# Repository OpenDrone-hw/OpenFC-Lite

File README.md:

# OpenFC Lite 30x30

Open source Betaflight flight controller built on the RP2354B, 30.5 x 30.5 mm
mounting pattern, part of the incutec OpenDrone line.

## Specifications

| | |
|---|---|
| Firmware | Betaflight |
| MCU | RP2354B |
| IMU | BMI270 |
| Barometer | None |
| Blackbox | microSD |
| OSD | Analog and digital |
| UARTs | 4 |
| General-purpose I/O | 4 PWM-capable pins (GPIO28-31) on the 8-pin connector; the Betaflight target runs bidirectional DShot on them |
| RX | External, CRSF or SBUS |
| Input | 3-8S* LiPo (9.0-33.6 V) |
| BEC | 10 V switchable + 5 V always-on, 3.5 A |
| Current sense | Yes |
| USB | USB-C |
| Mounting | 30.5 x 30.5 mm, 4.0 mm holes |
| Dimensions | 37.9 x 37.9 mm |
| PCB | 6-layer, 1.6 mm |

* Also runs on 2S; the 10 V VTX output then follows the battery voltage instead of holding 10 V.

Technical write-up, part list and layout constraints: [AGENTS.md](AGENTS.md).

## Firmware

Betaflight, target `OPENFC_LITE_RP2350B`. The image is in
[`firmware/`](firmware/); older ones are in `firmware/archive/`.

If the analog OSD stays blank, run `feature -LED_STRIP` and then `save` in the
Betaflight Configurator CLI (the LED strip is then off). A firmware update
that runs the OSD and the LED strip together is in progress.

## In the line

What pairs with what, and what is available:
[opendrone.be](https://opendrone.be).

## Contributing

See [CONTRIBUTING.md](CONTRIBUTING.md).

## License

Hardware licensed under [CERN-OHL-S-2.0](https://ohwr.org/cern_ohl_s_v2.txt),
see [LICENSE](LICENSE).

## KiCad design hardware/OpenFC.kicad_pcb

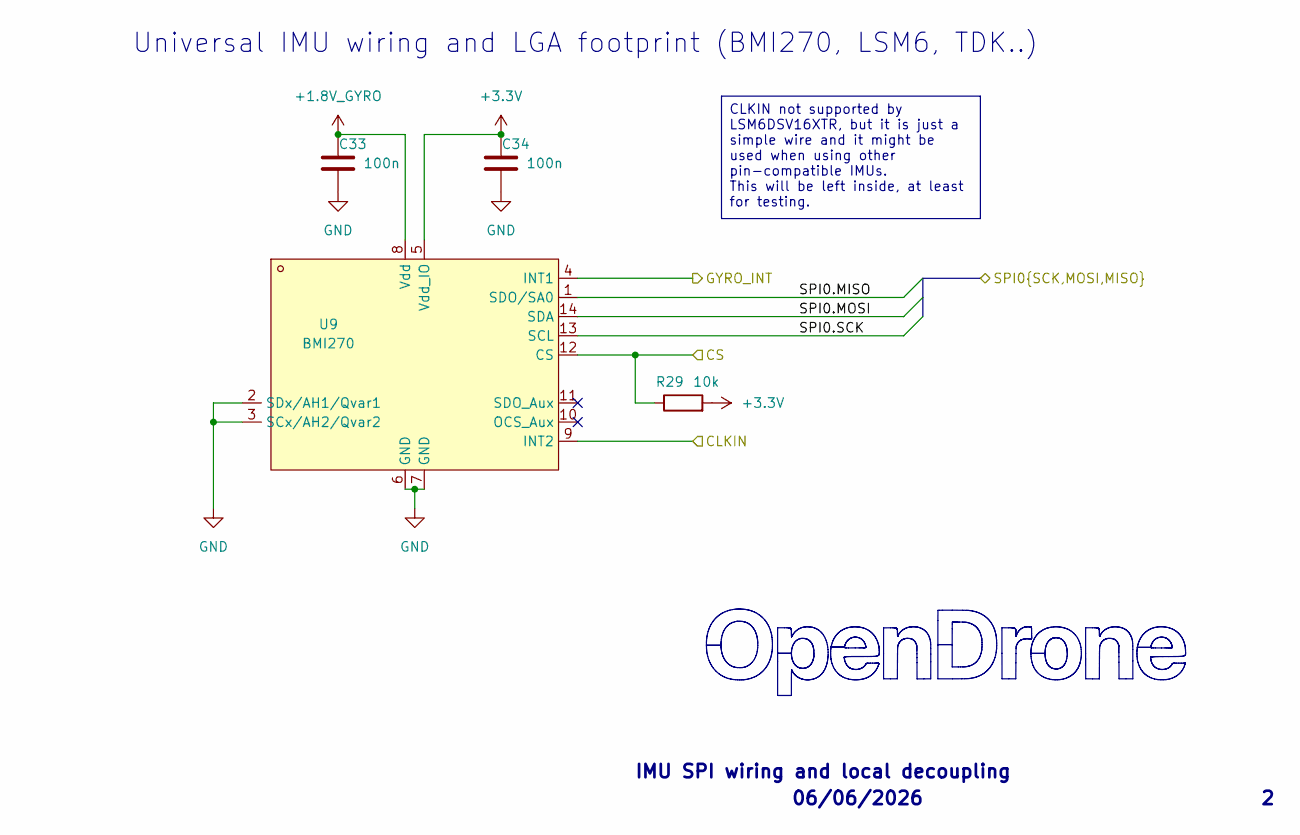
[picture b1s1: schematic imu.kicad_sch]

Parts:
C33, C34: 100n; C_0201_0603Metric; MPN GRM033R61E104KE14D; LCSC C76939
R29: 10k; R_0201_0603Metric; MPN RC0201FR-0710KL; LCSC C106225
U9: BMI270; LGA-14_L3.0-W2.5-P0.50-BR; MPN BMI270; LCSC C2836813

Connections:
+1.8V_GYRO: C33.1, U9.8 (Vdd); also elsewhere on the board
+3.3V: C34.1, R29.2, U9.5 (Vdd_IO); also elsewhere on the board
/IMU/CLKIN: U9.9 (INT2); also elsewhere on the board
/IMU/CS: R29.1, U9.12 (CS); also elsewhere on the board
/IMU/GYRO_INT: U9.4 (INT1); also elsewhere on the board
/IMU/SPI0.MISO: U9.1 (SDO/SA0); also elsewhere on the board
/IMU/SPI0.MOSI: U9.14 (SDA); also elsewhere on the board
/IMU/SPI0.SCK: U9.13 (SCL); also elsewhere on the board
GND: C33.2, C34.2, U9.2 (SDx/AH1/Qvar1), U9.3 (SCx/AH2/Qvar2), U9.6 (GND), U9.7 (GND); also elsewhere on the board

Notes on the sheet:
06/06/2026
IMU SPI wiring and local decoupling
Universal IMU wiring and LGA footprint (BMI270, LSM6, TDK..)
CLKIN not supported by LSM6DSV16XTR, but it is just a simple wire and it might be used when using other pin-compatible IMUs. This will be left inside, at least for testing.

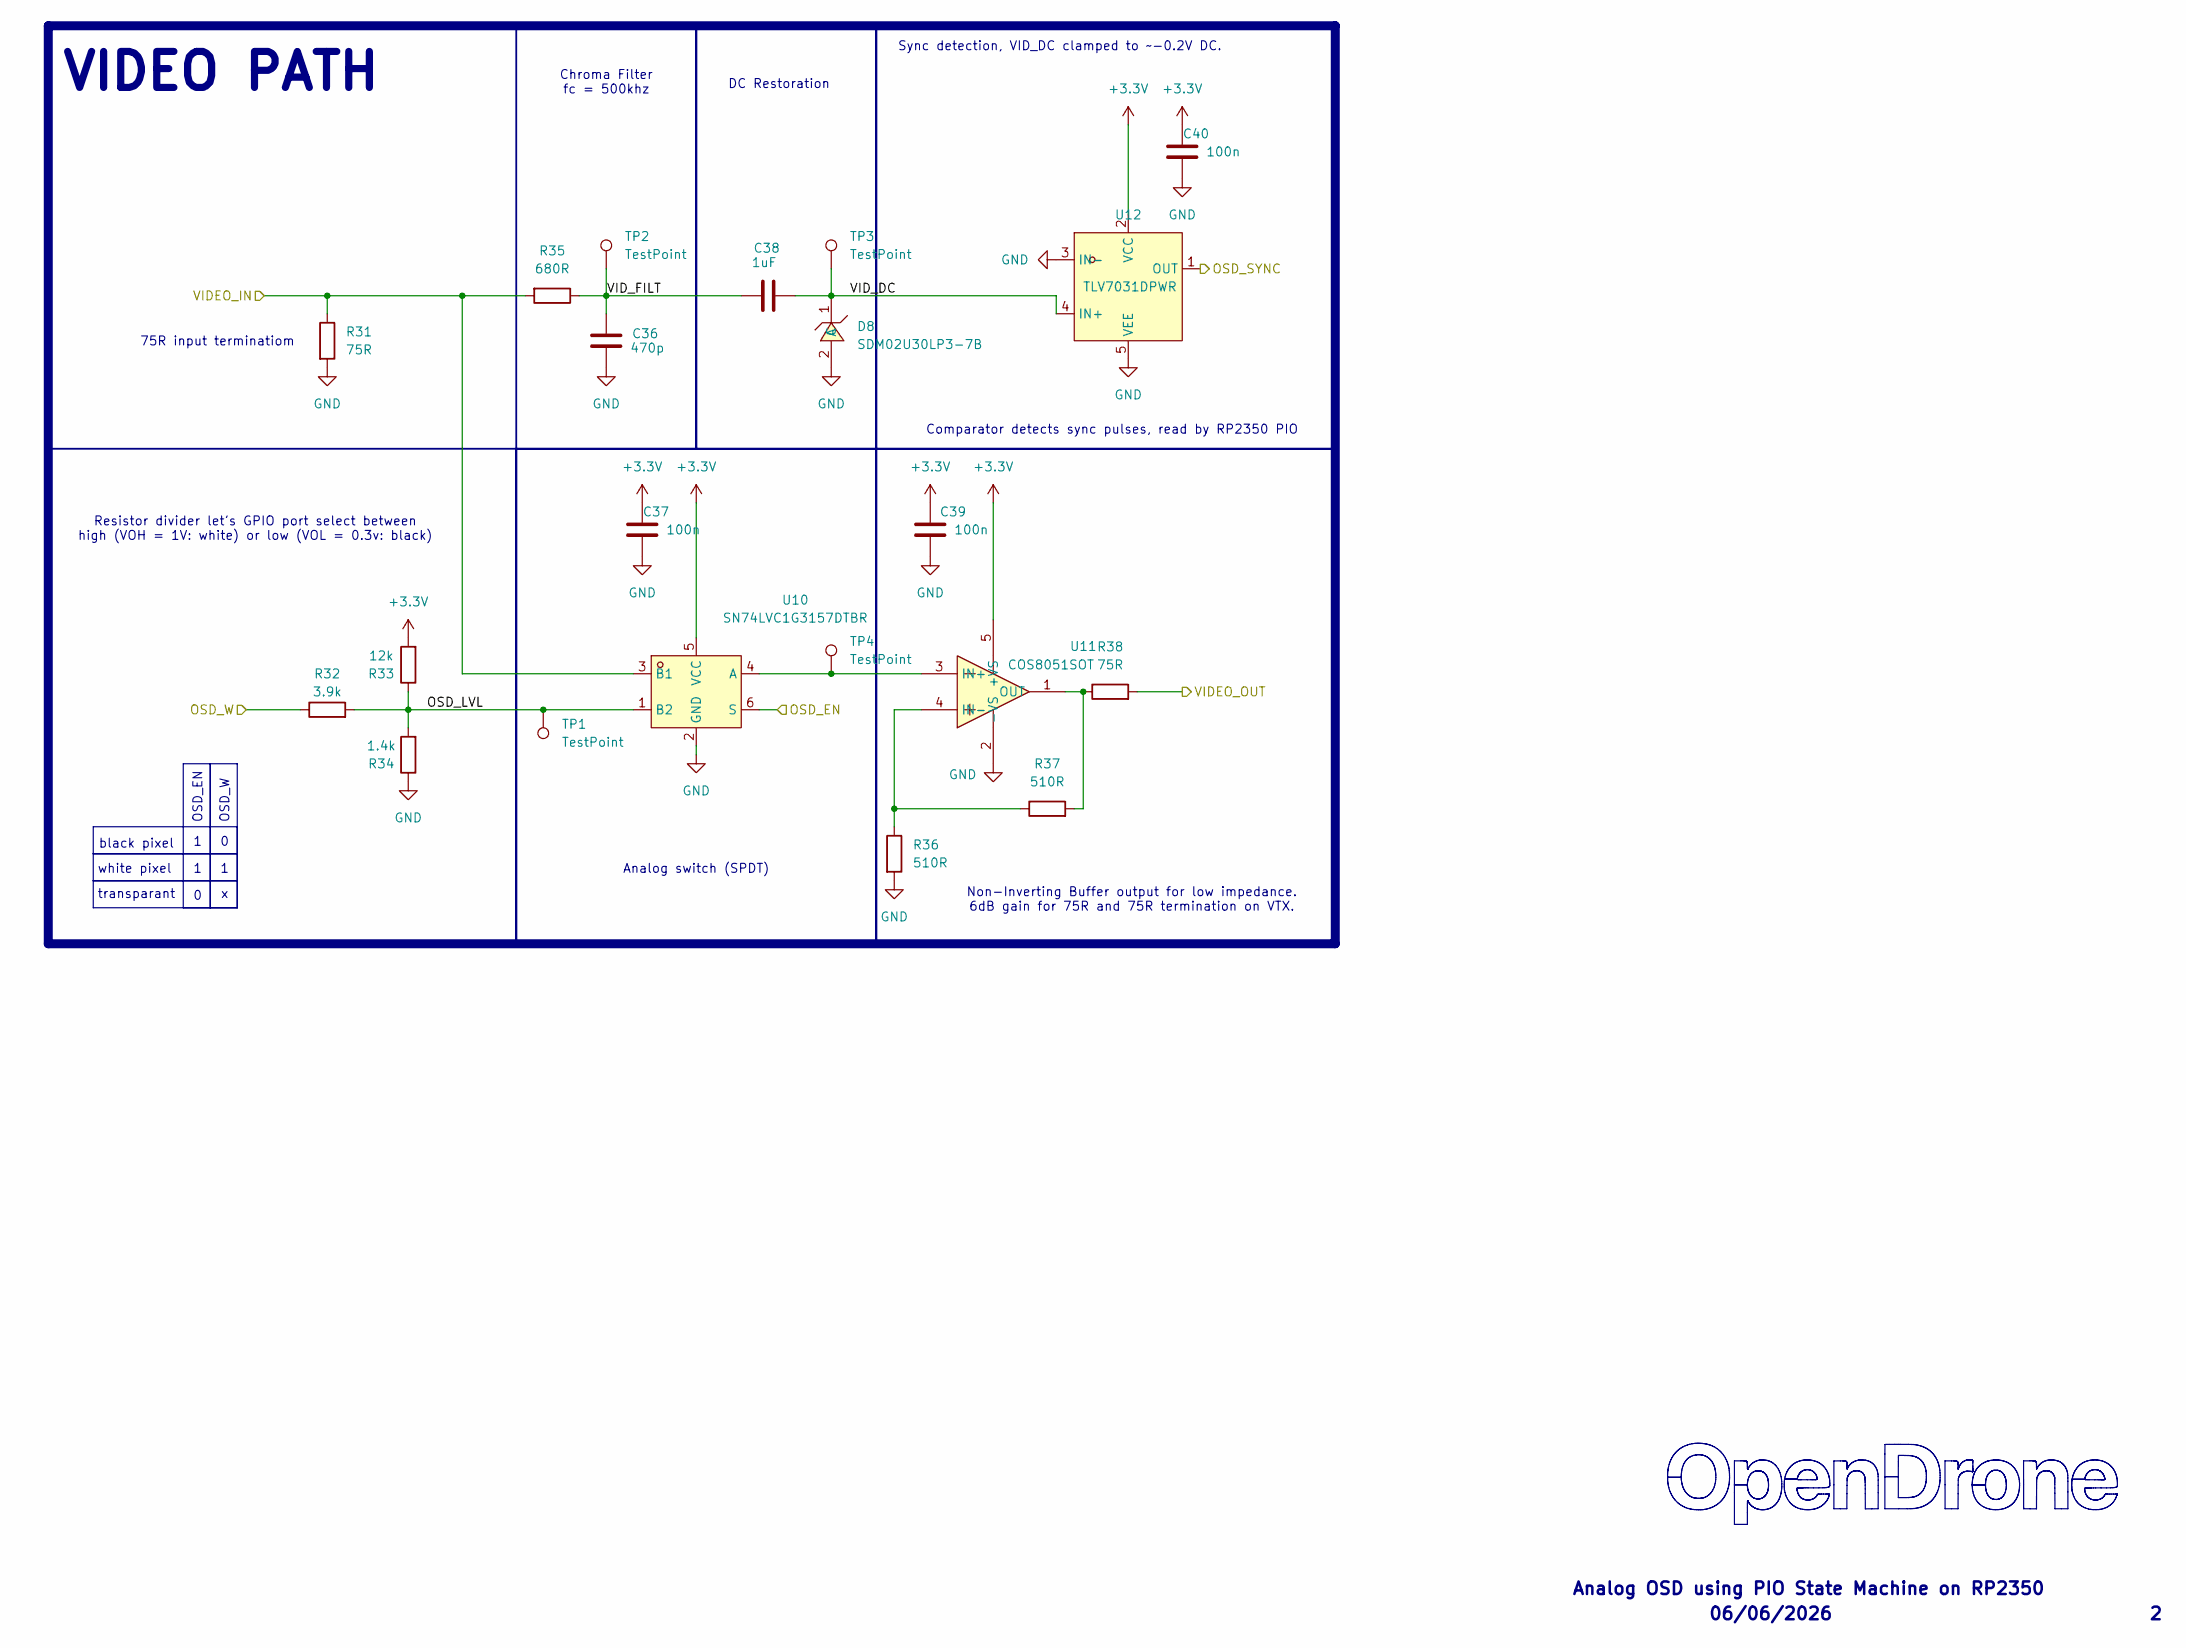
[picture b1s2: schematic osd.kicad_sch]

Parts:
C36: 470p; C_0201_0603Metric; MPN CC0201JRX7R9BB471; LCSC C526944
C37, C39, C40: 100n; C_0201_0603Metric; MPN GRM033R60J104KE19D; LCSC C76928
C38: 1uF; C_0402_1005Metric; MPN CL05A105KA5NQNC; LCSC C52923
D8: SDM02U30LP3-7B; X3-DFN0603-2_L0.6-W0.3-RD; MPN SDM02U30LP3-7B; LCSC C151629
R31, R38: 75R; R_0201_0603Metric; MPN RC0201FR-0775RL; LCSC C274878
R32: 3.9k; R_0201_0603Metric; MPN RC0201FR-073K9L; LCSC C273280
R33: 12k; R_0201_0603Metric; MPN 0201WMF1202TEE; LCSC C270363
R34: 1.4k; R_0201_0603Metric; MPN 0201WMF1401TEE; LCSC C423739
R35: 680R; R_0201_0603Metric; MPN 0201WMF6800TEE; LCSC C473509
R36, R37: 510R; R_0201_0603Metric; MPN RC0201FR-07510RL; LCSC C57784
TP1, TP2, TP3, TP4: TestPoint; TestPoint_Pad_D1.5mm
U10: SN74LVC1G3157DTBR; X2SON-6_L1.0-W0.8-BL; MPN SN74LVC1G3157DTBR; LCSC C2673087
U11: COS8051SOT; SOT-23-5_L3.0-W1.7-P0.95-LS2.8-BR; MPN COS8051SOT; LCSC C7463385
U12: TLV7031DPWR; X2SON-4_L0.8-W0.8-P0.48-TL-A; MPN TLV7031DPWR; LCSC C2876045

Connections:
+3.3V: C37.1, C39.1, C40.1, R33.2, U10.5 (VCC), U11.5 (+VS), U12.2 (VCC); also elsewhere on the board
/OSD/OSD_EN: U10.6 (S); also elsewhere on the board
/OSD/OSD_LVL: R32.2, R33.1, R34.2, TP1.1 (1_1), U10.1 (B2)
/OSD/OSD_SYNC: U12.1 (OUT); also elsewhere on the board
/OSD/OSD_W: R32.1; also elsewhere on the board
/OSD/VIDEO_IN: R31.1, R35.2, U10.3 (B1); also elsewhere on the board
/OSD/VIDEO_OUT: R38.2; also elsewhere on the board
/OSD/VID_DC: C38.2, D8.1 (C), TP3.1 (1_1), U12.4 (IN+)
/OSD/VID_FILT: C36.1, C38.1, R35.1, TP2.1 (1_1)
GND: C36.2, C37.2, C39.2, C40.2, D8.2 (A), R31.2, R34.1, R36.2, U10.2 (GND), U11.2 (-VS), U12.3 (IN-), U12.5 (VEE); also elsewhere on the board
unnamed: TP4.1 (1_1), U10.4 (A), U11.3 (IN+)
unnamed: R36.1, R37.1, U11.4 (IN-)
unnamed: R37.2, R38.1, U11.1 (OUT)

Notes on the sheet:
black pixel
Comparator detects sync pulses, read by RP2350 PIO
06/06/2026
Analog OSD using PIO State Machine on RP2350
Sync detection, VID_DC clamped to ~-0.2V DC.
Non-Inverting Buffer output for low impedance. 6dB gain for 75R and 75R termination on VTX.
white pixel
75R input terminatiom
OSD_W
Chroma Filter fc = 500khz
VIDEO PATH
Analog switch (SPDT)
OSD_EN
transparant
DC Restoration
Resistor divider let's GPIO port select between high (VOH = 1V: white) or low (VOL = 0.3v: black)

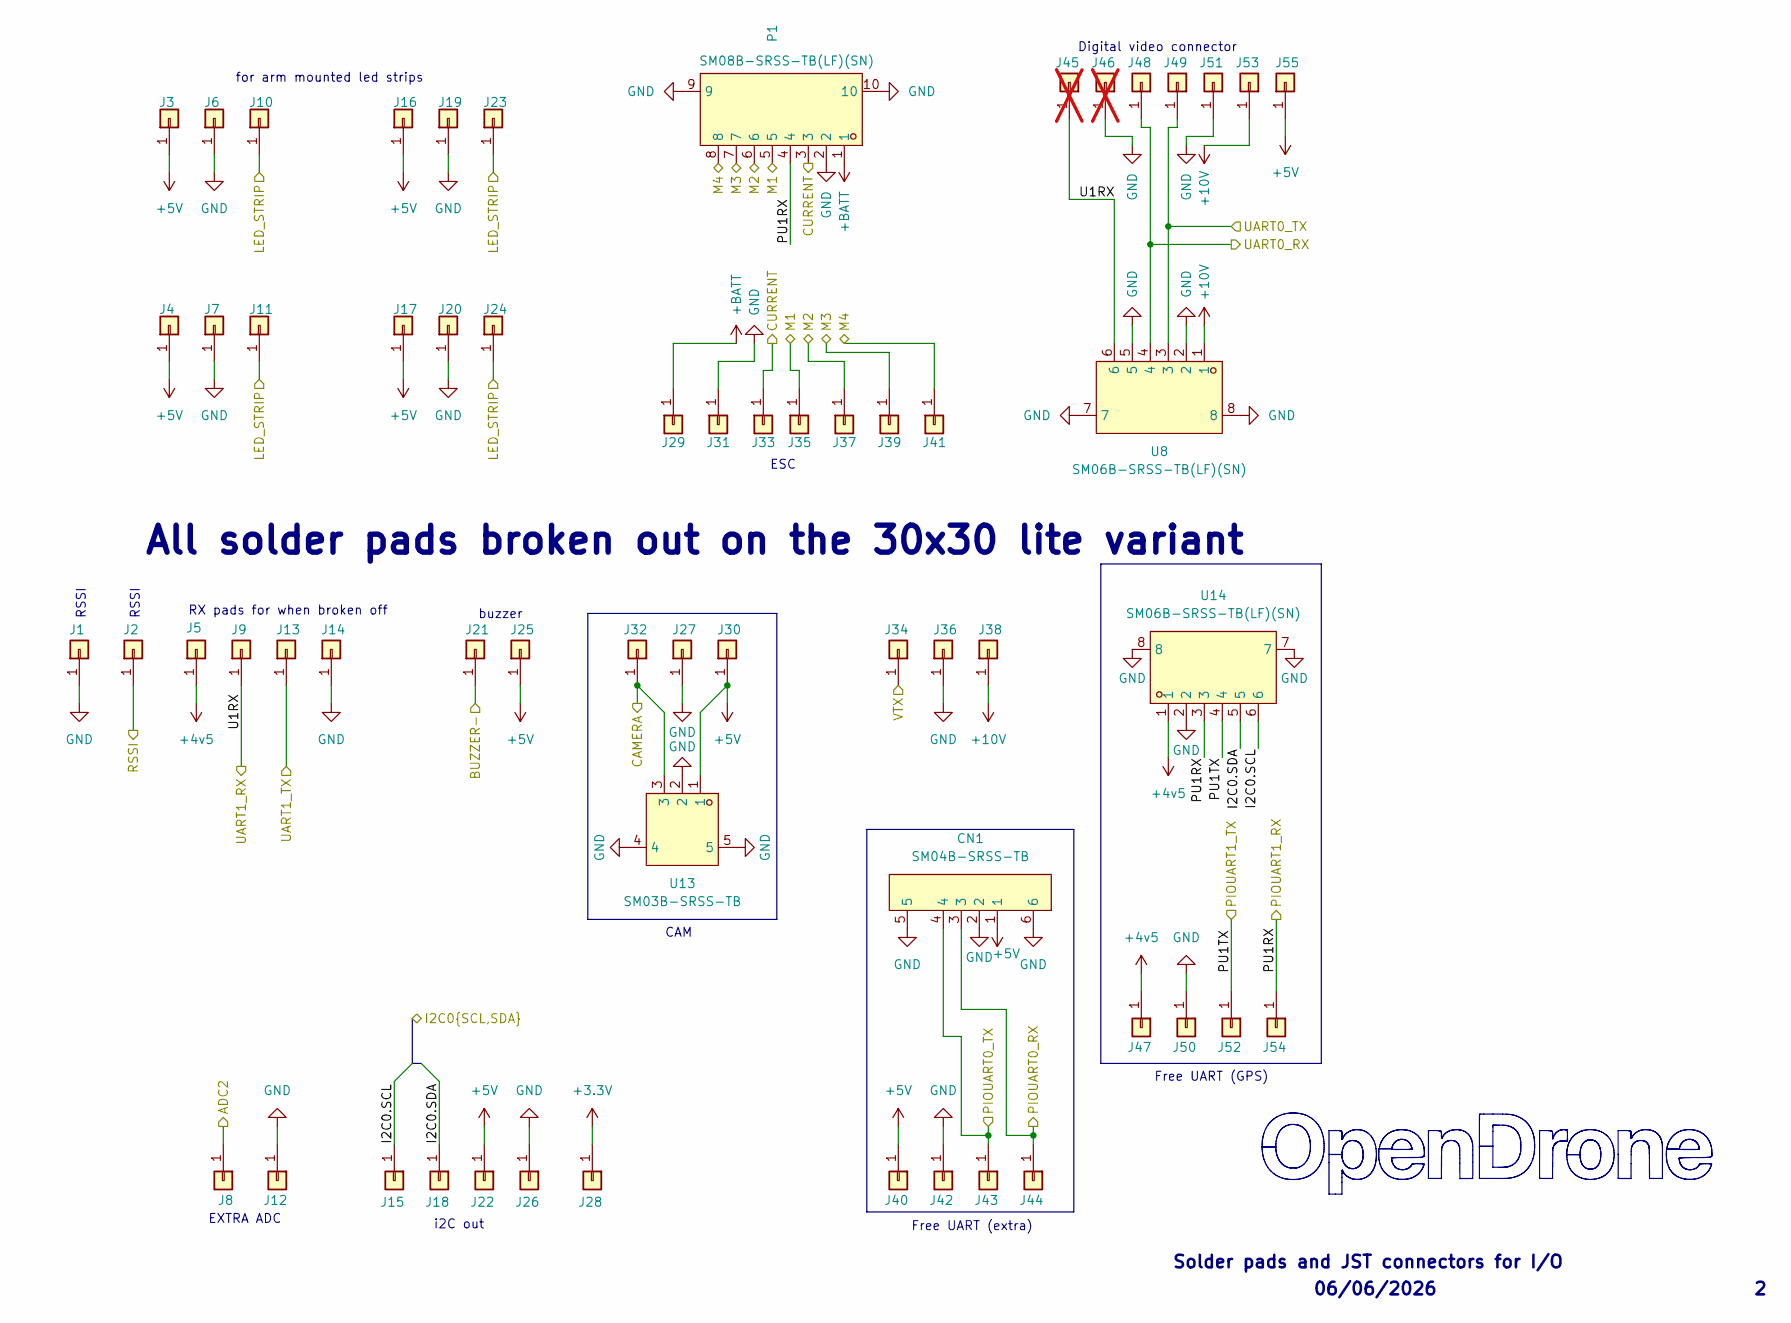
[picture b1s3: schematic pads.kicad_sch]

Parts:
CN1: SM04B-SRSS-TB; CONN-SMD_4P-P1.00_SM04B-SRSS-TB-LF-SN; MPN SM04B-SRSS-TB(LF)(SN); LCSC C160404
J1, J2, J3, J4, J5, J6, J7, J8, J9, J10, J11, J12, J13, J14, J15, J16, J17, J18, J19, J20, J21, J22, J23, J24, J25, J26, J27, J28, J29, J30, J31, J32, J33, J34, J35, J36, J37, J38, J39, J40, J41, J42, J43, J44, J47, J48, J49, J50, J51, J52, J53, J54, J55: 5V; small_pad
J45, J46: 5V; small_pad; not fitted
P1: SM08B-SRSS-TB(LF)(SN); CONN-TH_SM08B-SRSS-TB-LF-SN; MPN SM08B-SRSS-TB(LF)(SN); LCSC C160407
U8, U14: SM06B-SRSS-TB(LF)(SN); CONN-SMD_SM06B-SRSS-TB-LF-SN; MPN SM06B-SRSS-TB(LF)(SN); LCSC C160405
U13: SM03B-SRSS-TB; CONN-SMD_SM03B-SRSS-TB-LF-SN-P; MPN SM03B-SRSS-TB(LF)(SN); LCSC C160403

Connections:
+3.3V: J28.1 (Pin_1_1); also elsewhere on the board
+4v5: J5.1 (Pin_1_1), J47.1 (Pin_1_1), U14.1; also elsewhere on the board
+5V: CN1.1, J3.1 (Pin_1_1), J4.1 (Pin_1_1), J16.1 (Pin_1_1), J17.1 (Pin_1_1), J22.1 (Pin_1_1), J25.1 (Pin_1_1), J30.1 (Pin_1_1), J40.1 (Pin_1_1), J55.1 (Pin_1_1), U13.1; also elsewhere on the board
+10V: J38.1 (Pin_1_1), J53.1 (Pin_1_1), U8.1; also elsewhere on the board
+BATT: J29.1 (Pin_1_1), P1.1; also elsewhere on the board
/OSD/VIDEO_IN: J32.1 (Pin_1_1), U13.3; also elsewhere on the board
/OSD/VIDEO_OUT: J34.1 (Pin_1_1); also elsewhere on the board
/PADS/ADC2: J8.1 (Pin_1_1); also elsewhere on the board
/PADS/BUZZER-: J21.1 (Pin_1_1); also elsewhere on the board
/PADS/CURRENT: J33.1 (Pin_1_1), P1.3; also elsewhere on the board
/PADS/I2C0.SCL: J15.1 (Pin_1_1), U14.6; also elsewhere on the board
/PADS/I2C0.SDA: J18.1 (Pin_1_1), U14.5; also elsewhere on the board
/PADS/LED_STRIP: J10.1 (Pin_1_1), J11.1 (Pin_1_1), J23.1 (Pin_1_1), J24.1 (Pin_1_1); also elsewhere on the board
/PADS/M1: J35.1 (Pin_1_1), P1.5; also elsewhere on the board
/PADS/M2: J37.1 (Pin_1_1), P1.6; also elsewhere on the board
/PADS/M3: J39.1 (Pin_1_1), P1.7; also elsewhere on the board
/PADS/M4: J41.1 (Pin_1_1), P1.8; also elsewhere on the board
/PADS/PIOUART0_RX: CN1.3, J44.1 (Pin_1_1); also elsewhere on the board
/PADS/PIOUART0_TX: CN1.4, J43.1 (Pin_1_1); also elsewhere on the board
/PADS/PU1RX: J54.1 (Pin_1_1), P1.4, U14.3; also elsewhere on the board
/PADS/PU1TX: J52.1 (Pin_1_1), U14.4; also elsewhere on the board
/PADS/RSSI: J2.1 (Pin_1_1); also elsewhere on the board
/PADS/U1RX: J9.1 (Pin_1_1), J45.1, U8.6; also elsewhere on the board
/PADS/UART0_RX: J48.1 (Pin_1_1), U8.4; also elsewhere on the board
/PADS/UART0_TX: J49.1 (Pin_1_1), U8.3; also elsewhere on the board
/PADS/UART1_TX: J13.1 (Pin_1_1); also elsewhere on the board
GND: CN1.2, CN1.5, CN1.6, J1.1 (Pin_1_1), J6.1 (Pin_1_1), J7.1 (Pin_1_1), J12.1 (Pin_1_1), J14.1 (Pin_1_1), J19.1 (Pin_1_1), J20.1 (Pin_1_1), J26.1 (Pin_1_1), J27.1 (Pin_1_1), J31.1 (Pin_1_1), J36.1 (Pin_1_1), J42.1 (Pin_1_1), J46.1, J50.1 (Pin_1_1), J51.1 (Pin_1_1), P1.2, P1.9, P1.10, U8.2, U8.5, U8.7, U8.8, U13.2, U13.4, U13.5, U14.2, U14.7, U14.8; also elsewhere on the board

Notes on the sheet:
06/06/2026
RSSI
Free UART (extra)
Solder pads and JST connectors for I/O
i2C out
CAM
All solder pads broken out on the 30x30 lite variant
Free UART (GPS)
buzzer
RX pads for when broken off
ESC
Digital video connector
EXTRA ADC
for arm mounted led strips

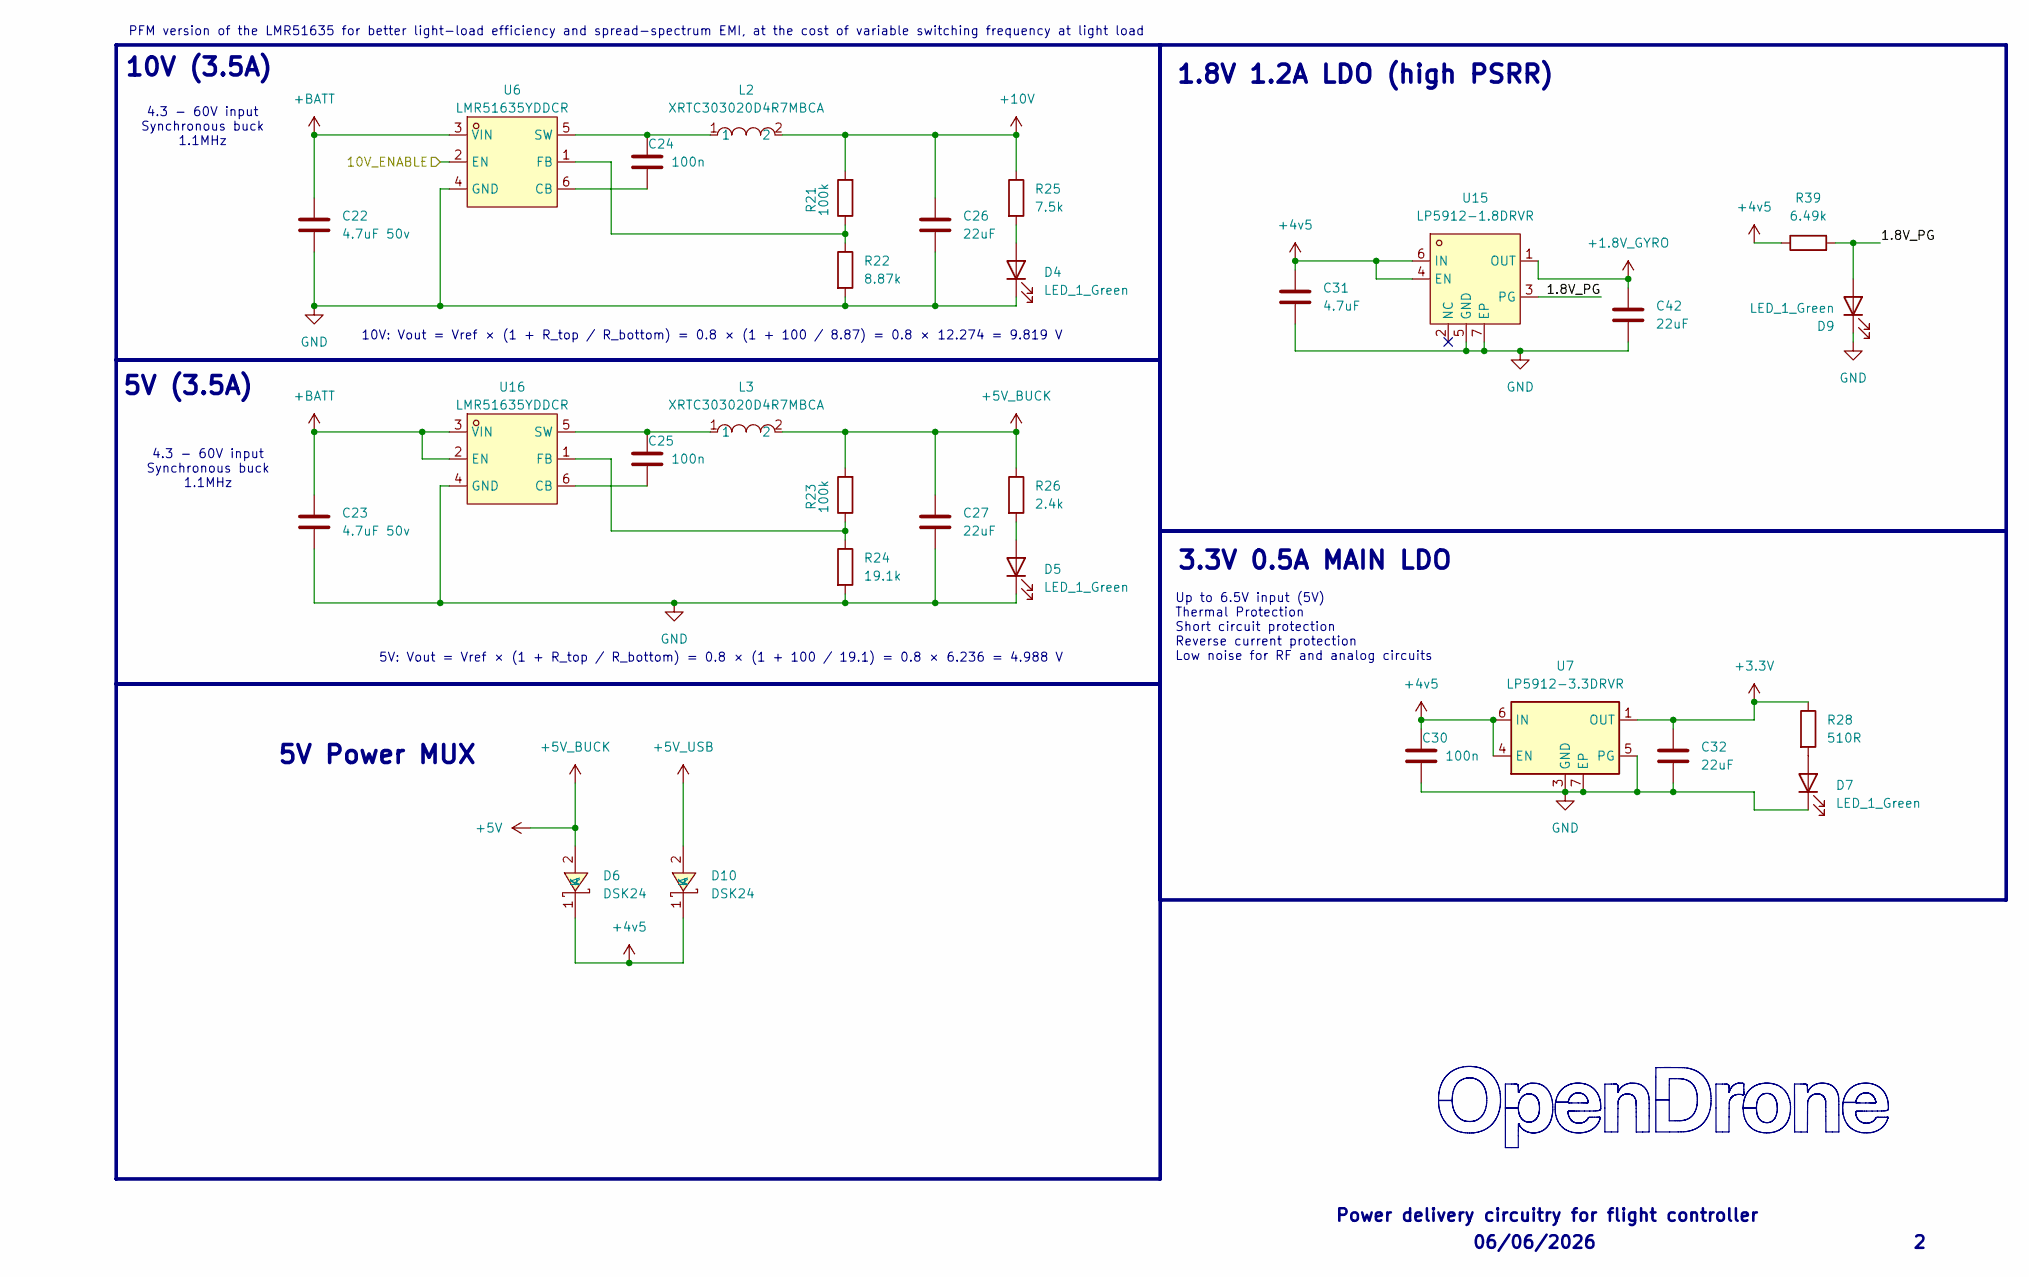
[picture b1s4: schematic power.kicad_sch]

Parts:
C22, C23: 4.7uF 50v; C_0805_2012Metric; MPN CL21A475KBQNNNE; LCSC C98192
C24, C25, C30: 100n; C_0201_0603Metric; MPN GRM033R61E104KE14D; LCSC C76939
C26, C27: 22uF; C_0603_1608Metric; MPN CL10A226MO7JZNC; LCSC C2762594
C31: 4.7uF; C_0402_1005Metric; MPN CL05A475MP5NRNC; LCSC C23733
C32: 22uF; C_0402_1005Metric; MPN CL05A226MQ5QUNC; LCSC C105226
C42: 22uF; C_0402_1005Metric; MPN GRM155R60J226ME11D; LCSC C415703
D4, D5, D7, D9: LED_1_Green; LED_0402_1005Metric; MPN XL-1005UGC; LCSC C965793
D6, D10: DSK24; SOD-123_L2.8-W1.8-LS3.7-RD; MPN DSK24; LCSC C64890
L2, L3: XRTC303020D4R7MBCA; IND-SMD_L3.0-W3.0_AFE303020S; MPN XRTC303020D4R7MBCA; LCSC C39846837
R21, R23: 100k; R_0201_0603Metric; MPN 0201WMF1003TEE; LCSC C270364
R22: 8.87k; R_0201_0603Metric; MPN RTT018871FTH; LCSC C332577
R24: 19.1k; R_0201_0603Metric; MPN RC-01W1912FT; LCSC C320741
R25: 7.5k; R_0201_0603Metric; MPN RC0201FR-077K5L; LCSC C474437
R26: 2.4k; R_0201_0603Metric; MPN RTT012401FTH; LCSC C166281
R28: 510R; R_0201_0603Metric; MPN RC0201FR-07510RL; LCSC C57784
R39: 6.49k; R_0201_0603Metric; MPN AF0201FR-076K49L; LCSC C2107920
U6, U16: LMR51635YDDCR; SOT-23-6_L2.9-W1.6-P0.95-LS2.8-BL; MPN LMR51635YDDCR; LCSC C45262770
U7: LP5912-3.3DRVR; WSON-6-1EP_2x2mm_P0.65mm_EP1x1.6mm; MPN LP5912-3.3DRVR; LCSC C524780
U15: LP5912-1.8DRVR; WSON-6-1EP_2x2mm_P0.65mm_EP1x1.6mm_ThermalVias; MPN LP5912-1.8DRVR; LCSC C2876234

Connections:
+1.8V_GYRO: C42.1, U15.1 (OUT); also elsewhere on the board
+3.3V: C32.1, R28.1, U7.1 (OUT); also elsewhere on the board
+4v5: C30.1, C31.1, D6.1 (K), D10.1 (K), R39.1, U7.4 (EN), U7.6 (IN), U15.4 (EN), U15.6 (IN); also elsewhere on the board
+5V: C27.1, D6.2 (A), L3.2, R23.2, R26.1; also elsewhere on the board
+5V_USB: D10.2 (A); also elsewhere on the board
+10V: C26.1, L2.2, R21.2, R25.1; also elsewhere on the board
+BATT: C22.1, C23.1, U6.3 (VIN), U16.2 (EN), U16.3 (VIN); also elsewhere on the board
/POWER/1.8V_PG: D9.2 (A), R39.2, U15.3 (PG)
/POWER/10V_ENABLE: U6.2 (EN); also elsewhere on the board
GND: C22.2, C23.2, C26.2, C27.2, C30.2, C31.2, C32.2, C42.2, D4.1 (K), D5.1 (K), D7.1 (K), D9.1 (K), R22.2, R24.2, U6.4 (GND), U7.3 (GND), U7.5 (PG), U7.7 (EP), U15.5 (GND), U15.7 (EP), U16.4 (GND); also elsewhere on the board
unnamed: D4.2 (A), R25.2
unnamed: D5.2 (A), R26.2
unnamed: D7.2 (A), R28.2
unnamed: C24.2, U6.6 (CB)
unnamed: R21.1, R22.1, U6.1 (FB)
unnamed: C24.1, L2.1, U6.5 (SW)
unnamed: C25.2, U16.6 (CB)
unnamed: R23.1, R24.1, U16.1 (FB)
unnamed: C25.1, L3.1, U16.5 (SW)

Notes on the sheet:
5V Power MUX
4.3 - 60V input Synchronous buck 1.1MHz
Power delivery circuitry for flight controller
06/06/2026
10V: Vout = Vref × (1 + R_top / R_bottom) = 0.8 × (1 + 100 / 8.87) = 0.8 × 12.274 = 9.819 V
5V: Vout = Vref × (1 + R_top / R_bottom) = 0.8 × (1 + 100 / 19.1) = 0.8 × 6.236 = 4.988 V
Up to 6.5V input (5V) Thermal Protection Short circuit protection Reverse current protection Low noise for RF and analog circuits
5V (3.5A)
1.8V 1.2A LDO (high PSRR)
PFM version of the LMR51635 for better light-load efficiency and spread-spectrum EMI, at the cost of variable switching frequency at light load
10V (3.5A)
3.3V 0.5A MAIN LDO
